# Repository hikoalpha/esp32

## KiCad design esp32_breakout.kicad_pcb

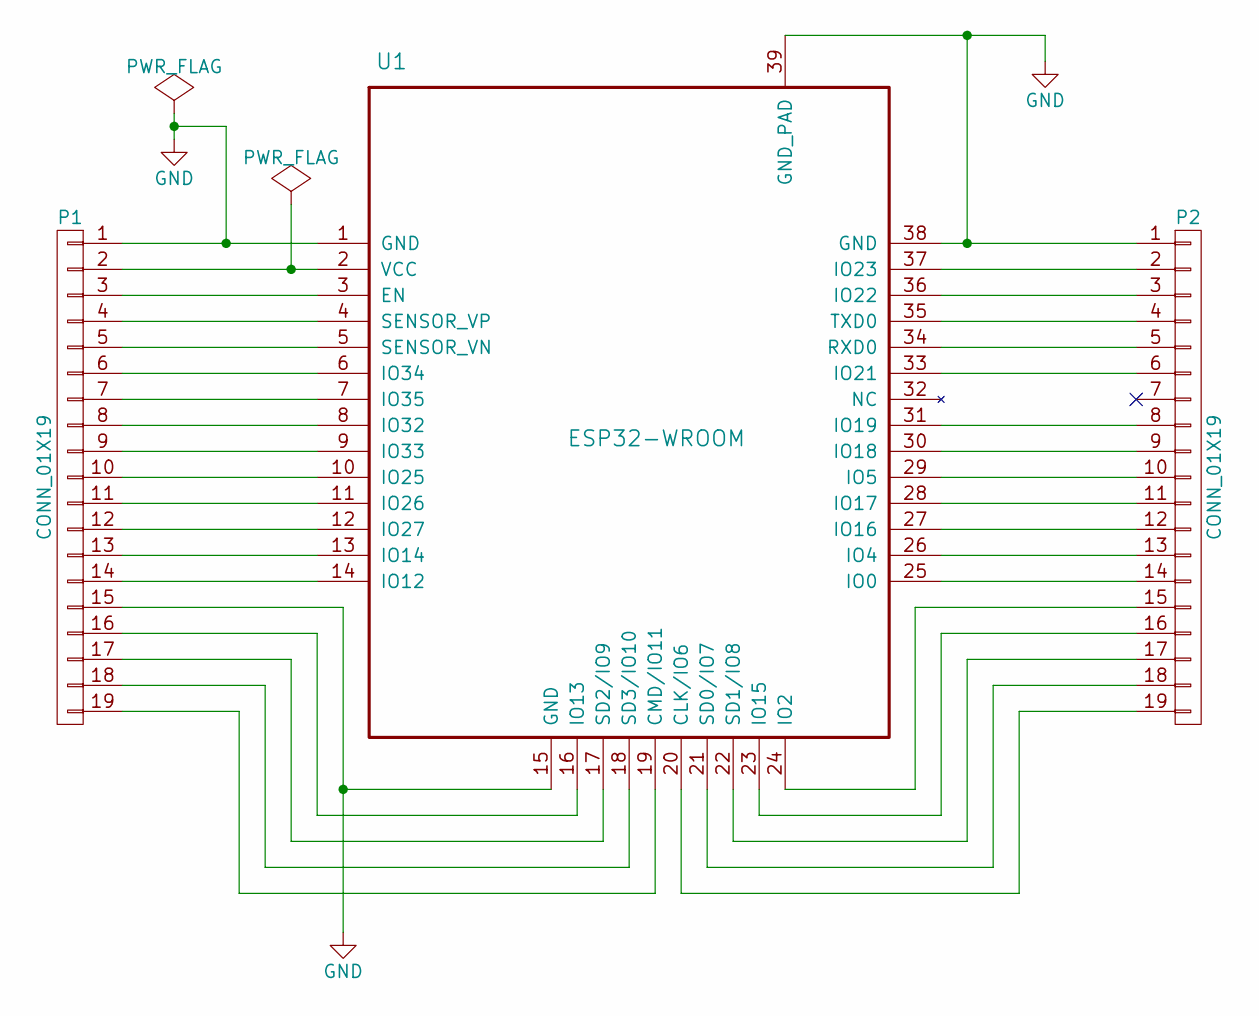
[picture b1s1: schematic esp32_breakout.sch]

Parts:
P1, P2: CONN_01X19; Pin_Header_Straight_1x19_Pitch2.54mm
U1: ESP32-WROOM

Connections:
GND: P1.1, P1.15, P2.1, U1.1 (GND), U1.15 (GND), U1.38 (GND), U1.39 (GND_PAD)
unnamed: P1.2, U1.2 (VCC)
unnamed: P1.3, U1.3 (EN)
unnamed: P1.4, U1.4 (SENSOR_VP)
unnamed: P1.5, U1.5 (SENSOR_VN)
unnamed: P1.6, U1.6 (IO34)
unnamed: P1.7, U1.7 (IO35)
unnamed: P1.8, U1.8 (IO32)
unnamed: P1.9, U1.9 (IO33)
unnamed: P1.10, U1.10 (IO25)
unnamed: P1.11, U1.11 (IO26)
unnamed: P1.12, U1.12 (IO27)
unnamed: P1.13, U1.13 (IO14)
unnamed: P1.14, U1.14 (IO12)
unnamed: P1.16, U1.16 (IO13)
unnamed: P1.17, U1.17 (SD2/IO9)
unnamed: P1.18, U1.18 (SD3/IO10)
unnamed: P1.19, U1.19 (CMD/IO11)
unnamed: P2.2, U1.37 (IO23)
unnamed: P2.3, U1.36 (IO22)
unnamed: P2.4, U1.35 (TXD0)
unnamed: P2.5, U1.34 (RXD0)
unnamed: P2.6, U1.33 (IO21)
unnamed: P2.8, U1.31 (IO19)
unnamed: P2.9, U1.30 (IO18)
unnamed: P2.10, U1.29 (IO5)
unnamed: P2.11, U1.28 (IO17)
unnamed: P2.12, U1.27 (IO16)
unnamed: P2.13, U1.26 (IO4)
unnamed: P2.14, U1.25 (IO0)
unnamed: P2.15, U1.24 (IO2)
unnamed: P2.16, U1.23 (IO15)
unnamed: P2.17, U1.22 (SD1/IO8)
unnamed: P2.18, U1.21 (SD0/IO7)
unnamed: P2.19, U1.20 (CLK/IO6)

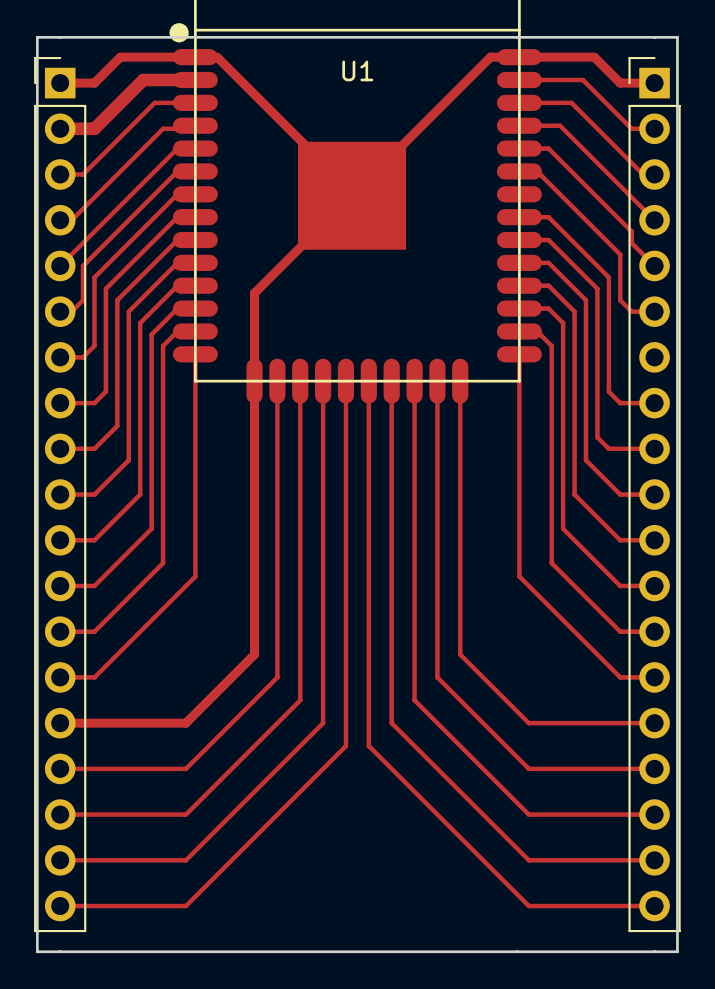
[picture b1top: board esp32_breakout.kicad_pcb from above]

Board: 2 copper layers, 35.6 x 50.8 mm, 3 parts (0 on the bottom side), 35 nets.
